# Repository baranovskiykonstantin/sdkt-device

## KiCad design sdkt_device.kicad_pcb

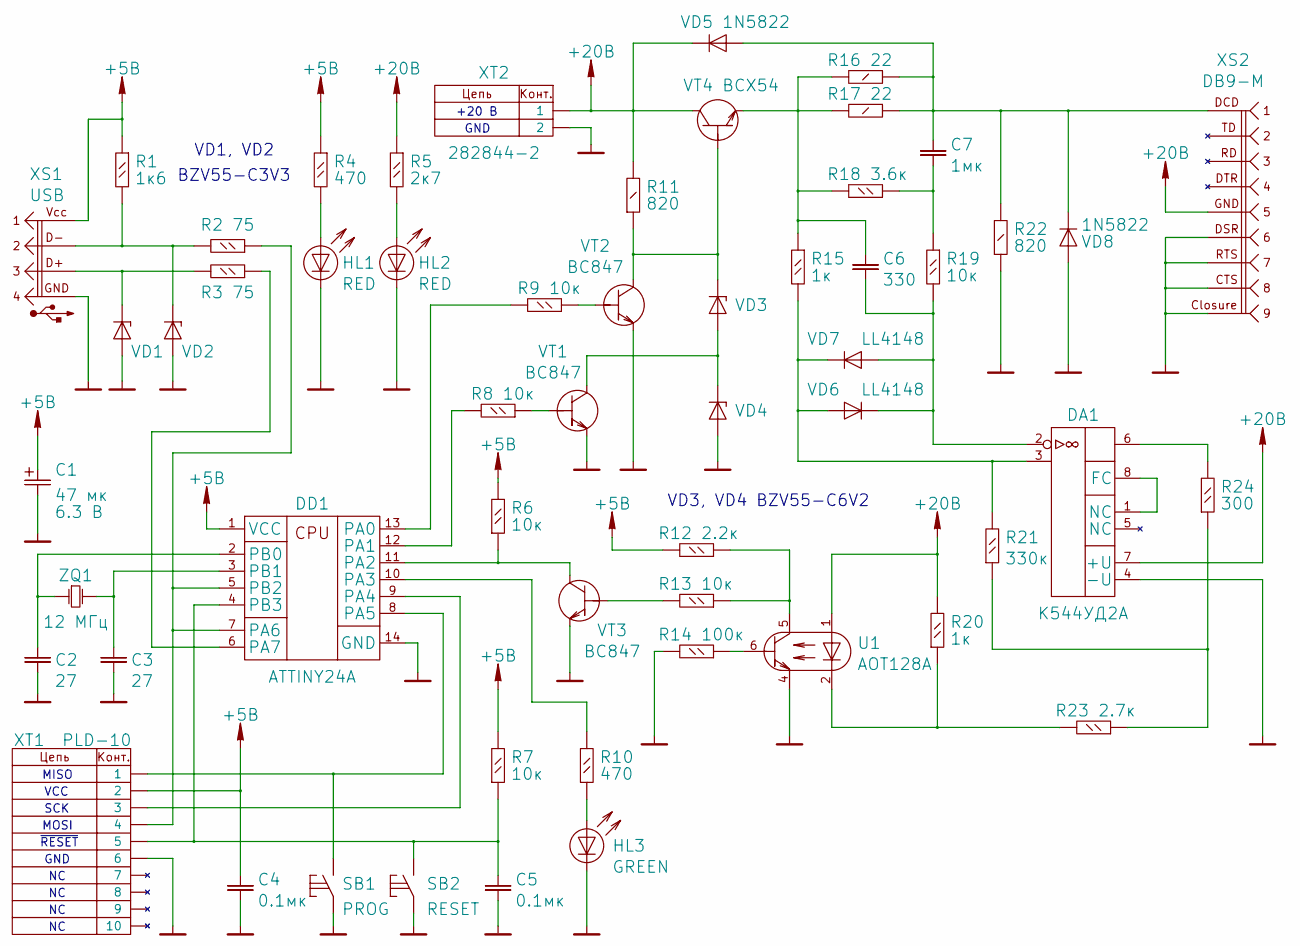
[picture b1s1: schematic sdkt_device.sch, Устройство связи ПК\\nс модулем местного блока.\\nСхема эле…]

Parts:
C1: 47 мк; SMA
C2, C3: 27
C4, C5: 0.1мк
C6: 330
C7: 1мк
DA1: К544УД2А
DD1: ATTINY24A; SO14
HL1, HL2: RED
HL3: GREEN
R1: 1к6
R2, R3: 75
R4, R10: 470
R5: 2к7
R6, R7, R8, R9, R13, R19: 10к
R11, R22: 820
R12: 2.2к
R14: 100к
R15, R20: 1к
R16, R17: 22
R18: 3.6к
R21: 330к
R23: 2.7к
R24: 300
SB1: SWT-2
SB2: SWT-6
U1: AOT128A
VD1, VD2: BZV55-C3V3
VD3, VD4: BZV55-C6V2; SOD80
VD5, VD8: 1N5822
VD6, VD7: LL4148
VT1, VT2, VT3: BC847
VT4: BCX54; SOT89
XS1: USB
XS2: DB9-M
XT1: PLD-10
XT2: 282844-2
ZQ1: 12 МГц

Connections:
+5B: C1.1, C4.2, DD1.1 (VCC), R1.1, R4.1, R6.2, R7.2, R12.2, XS1.1 (VCC), XT1.2
+20B: DA1.7 (+U), R5.1, R11.2, R20.2, U1.1 (A), VD5.2 (K), VT4.2 (C), XS2.5 (GND), XT2.1
GND: C1.2, C2.1, C3.1, C4.1, C5.1, DA1.4 (-U), DD1.14 (GND), HL1.2 (K), HL2.2 (K), HL3.2 (K), R14.2, R22.1, SB1.2 (L2), SB2.2 (L2), U1.4 (E), VD1.1 (A), VD2.1 (A), VD4.1 (A), VD8.1 (A), VT1.2 (E), VT2.2 (E), VT3.2 (E), XS1.4 (GND), XS2.6 (DSR), XS2.7 (RTS), XS2.8 (CTS), XS2.9 (Closure), XT1.6, XT2.2
unnamed: C2.2, DD1.2 (PB0), ZQ1.1
unnamed: C3.2, DD1.3 (PB1), ZQ1.2
unnamed: C5.2, DD1.4 (PB3), R7.1, SB2.1 (L1), XT1.5
unnamed: C6.1, DA1.2, R19.2, VD6.2 (K), VD7.1 (A)
unnamed: C6.2, R15.1, R16.2, R17.2, R18.2, VT4.1 (E)
unnamed: C7.1, R16.1, R17.1, R22.2, VD5.1 (A), VD8.2 (K), XS2.1 (DCD)
unnamed: C7.2, R18.1, R19.1
unnamed: DA1.1 (NC), DA1.8 (FC)
unnamed: DA1.3, R15.2, R21.2, VD6.1 (A), VD7.2 (K)
unnamed: DA1.6, R24.2
unnamed: DD1.5 (PB2), DD1.7 (PA6), R2.1, XT1.4
unnamed: DD1.6 (PA7), R3.1
unnamed: DD1.8 (PA5), SB1.1 (L1), XT1.1
unnamed: DD1.9 (PA4), XT1.3
unnamed: DD1.10 (PA3), R10.2
unnamed: DD1.11 (PA2), R6.1, VT3.3 (C)
unnamed: DD1.12 (PA1), R8.2
unnamed: DD1.13 (PA0), R9.2
unnamed: HL1.1 (A), R4.2
unnamed: HL2.1 (A), R5.2
unnamed: HL3.1 (A), R10.1
unnamed: R1.2, R2.2, VD2.2 (K), XS1.2 (D-)
unnamed: R3.2, VD1.2 (K), XS1.3 (D+)
unnamed: R8.1, VT1.1 (B)
unnamed: R9.1, VT2.1 (B)
unnamed: R11.1, VD3.2 (K), VT2.3 (C), VT4.3 (B)
unnamed: R12.1, R13.1, U1.5 (C)
unnamed: R13.2, VT3.1 (B)
unnamed: R14.1, U1.6 (B)
unnamed: R20.1, R23.2, U1.2 (K)
unnamed: R21.1, R23.1, R24.1
unnamed: VD3.1 (A), VD4.2 (K), VT1.3 (C)

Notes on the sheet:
VD3, VD4 BZV55-C6V2
MISO
MOSI
VCC
SCK
~RESET
GND
+20 В
VD1, VD2
BZV55-C3V3

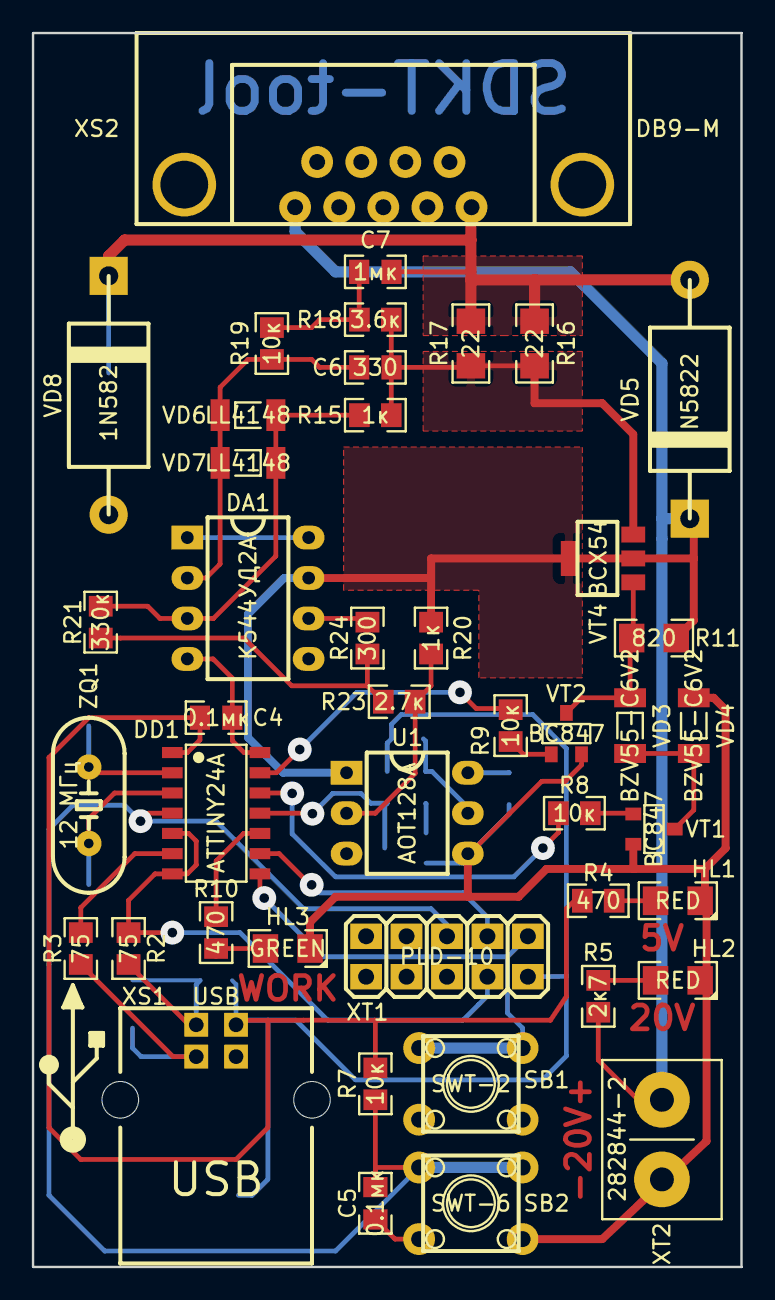
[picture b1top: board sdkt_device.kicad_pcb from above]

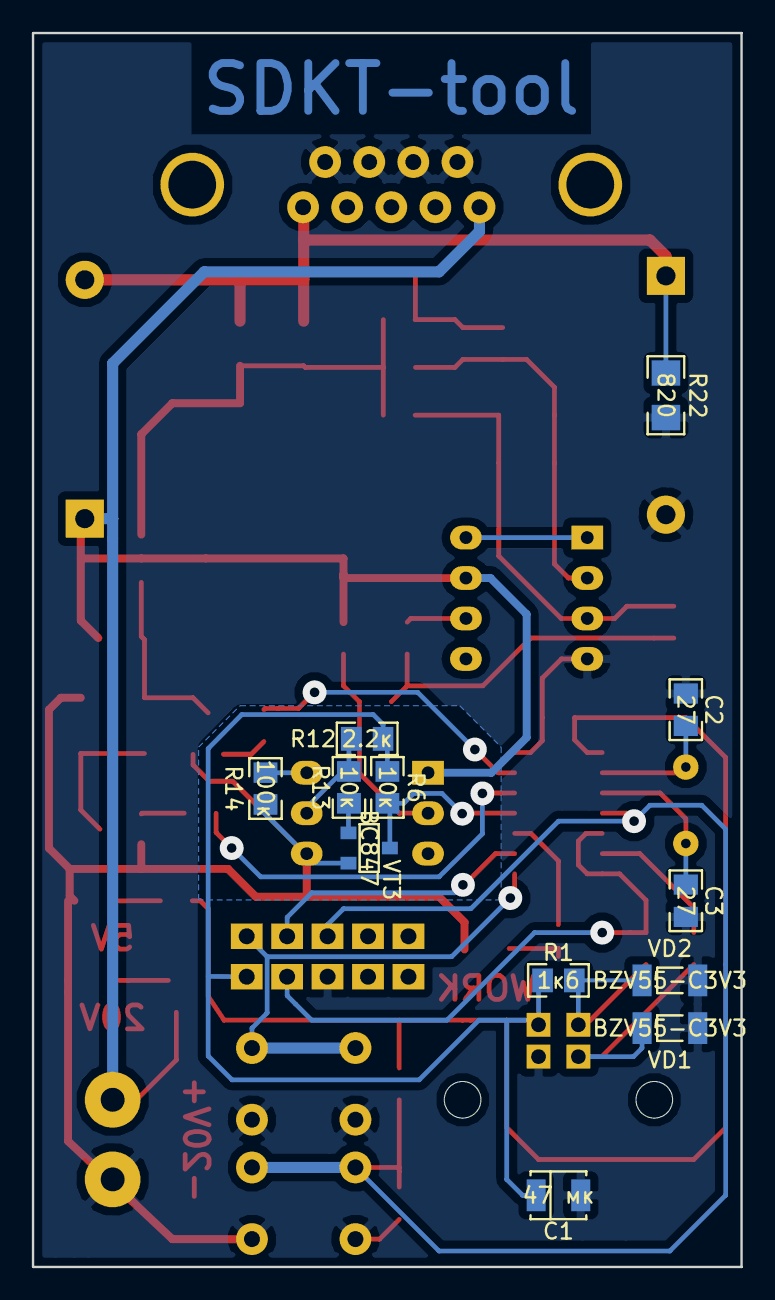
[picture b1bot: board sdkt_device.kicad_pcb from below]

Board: 2 copper layers, 44.5 x 77.5 mm, 56 parts (12 on the bottom side), 35 nets.

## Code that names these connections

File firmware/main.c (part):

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
// Обозначения портов и линий ввода/вывода
#define OUTPUT            PORTA
#define LED               PA3
#define STEP0             PA0
#define STEP1             PA1

// Значения задержек, мс
#define DELAY_RES         2
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  //----------------------------------------------------------------------------
  // Прерывания
  //----------------------------------------------------------------------------
  PCMSK0 |= (1 << PCINT2);  // Входной сигнал подключен к PA2
  TCCR1B |= (1 << CS10);    // Таймер1 без предв. делителя

  //----------------------------------------------------------------------------
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
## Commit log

2014-10-03 Starts control of project with Git.
